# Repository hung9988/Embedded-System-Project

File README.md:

# HUST Embedded Systems Project
This is a project for the course of Embedded Systems at HUST.

## Project Overview
This project focus on the design of a analog macro pad using the Blackpill (STM32F411CEU6) microcontroller. 

## Features
- **Analog Output**: The macro pad can output analog signals.
- **Rapid Trigger**: A feature that allows the macro pad to send a signal immediately when a key is pressed, without waiting for the key to be released.
- **USB HID**: The macro pad will be recognized as a Human Interface Device (HID) by the host computer, allowing it to send key presses and other input events.
- **USB CDC**: The macro pad will support USB Communication Device Class (CDC) for serial communication with the host computer.
- **Macro Support**: The macro pad can be programmed to perform specific actions when certain keys are pressed.
## External Links
- [3D Case Design](https://cad.onshape.com/documents/5e6cfea2e32c850f530cae58/w/579554a927bd0a7730e0b539/e/56addd2516469d5755cfe071?renderMode=0&uiState=685a2b979b232715eddfcd3f)

## Resources

- [How does USB work?](https://www.youtube.com/watch?v=N0O5Uwc3C0o&t=158s)
- [What is Rapid Trigger?](https://www.youtube.com/watch?v=eZENx1T7OLw)

## References

- [Minipad](https://github.com/minipadKB/minipad-firmware)
- [Riskeyboard](https://github.com/riskable/void_switch_65_pct)
- [Macrolev](https://github.com/heiso/macrolev/tree/main)
- [TinyUSB](https://github.com/hathach/tinyusb)
- [USB in a Nutshell](https://www.beyondlogic.org/usbnutshell/usb1.shtml)
- [SSD1306](https://github.com/afiskon/stm32-ssd1306/tree/master)

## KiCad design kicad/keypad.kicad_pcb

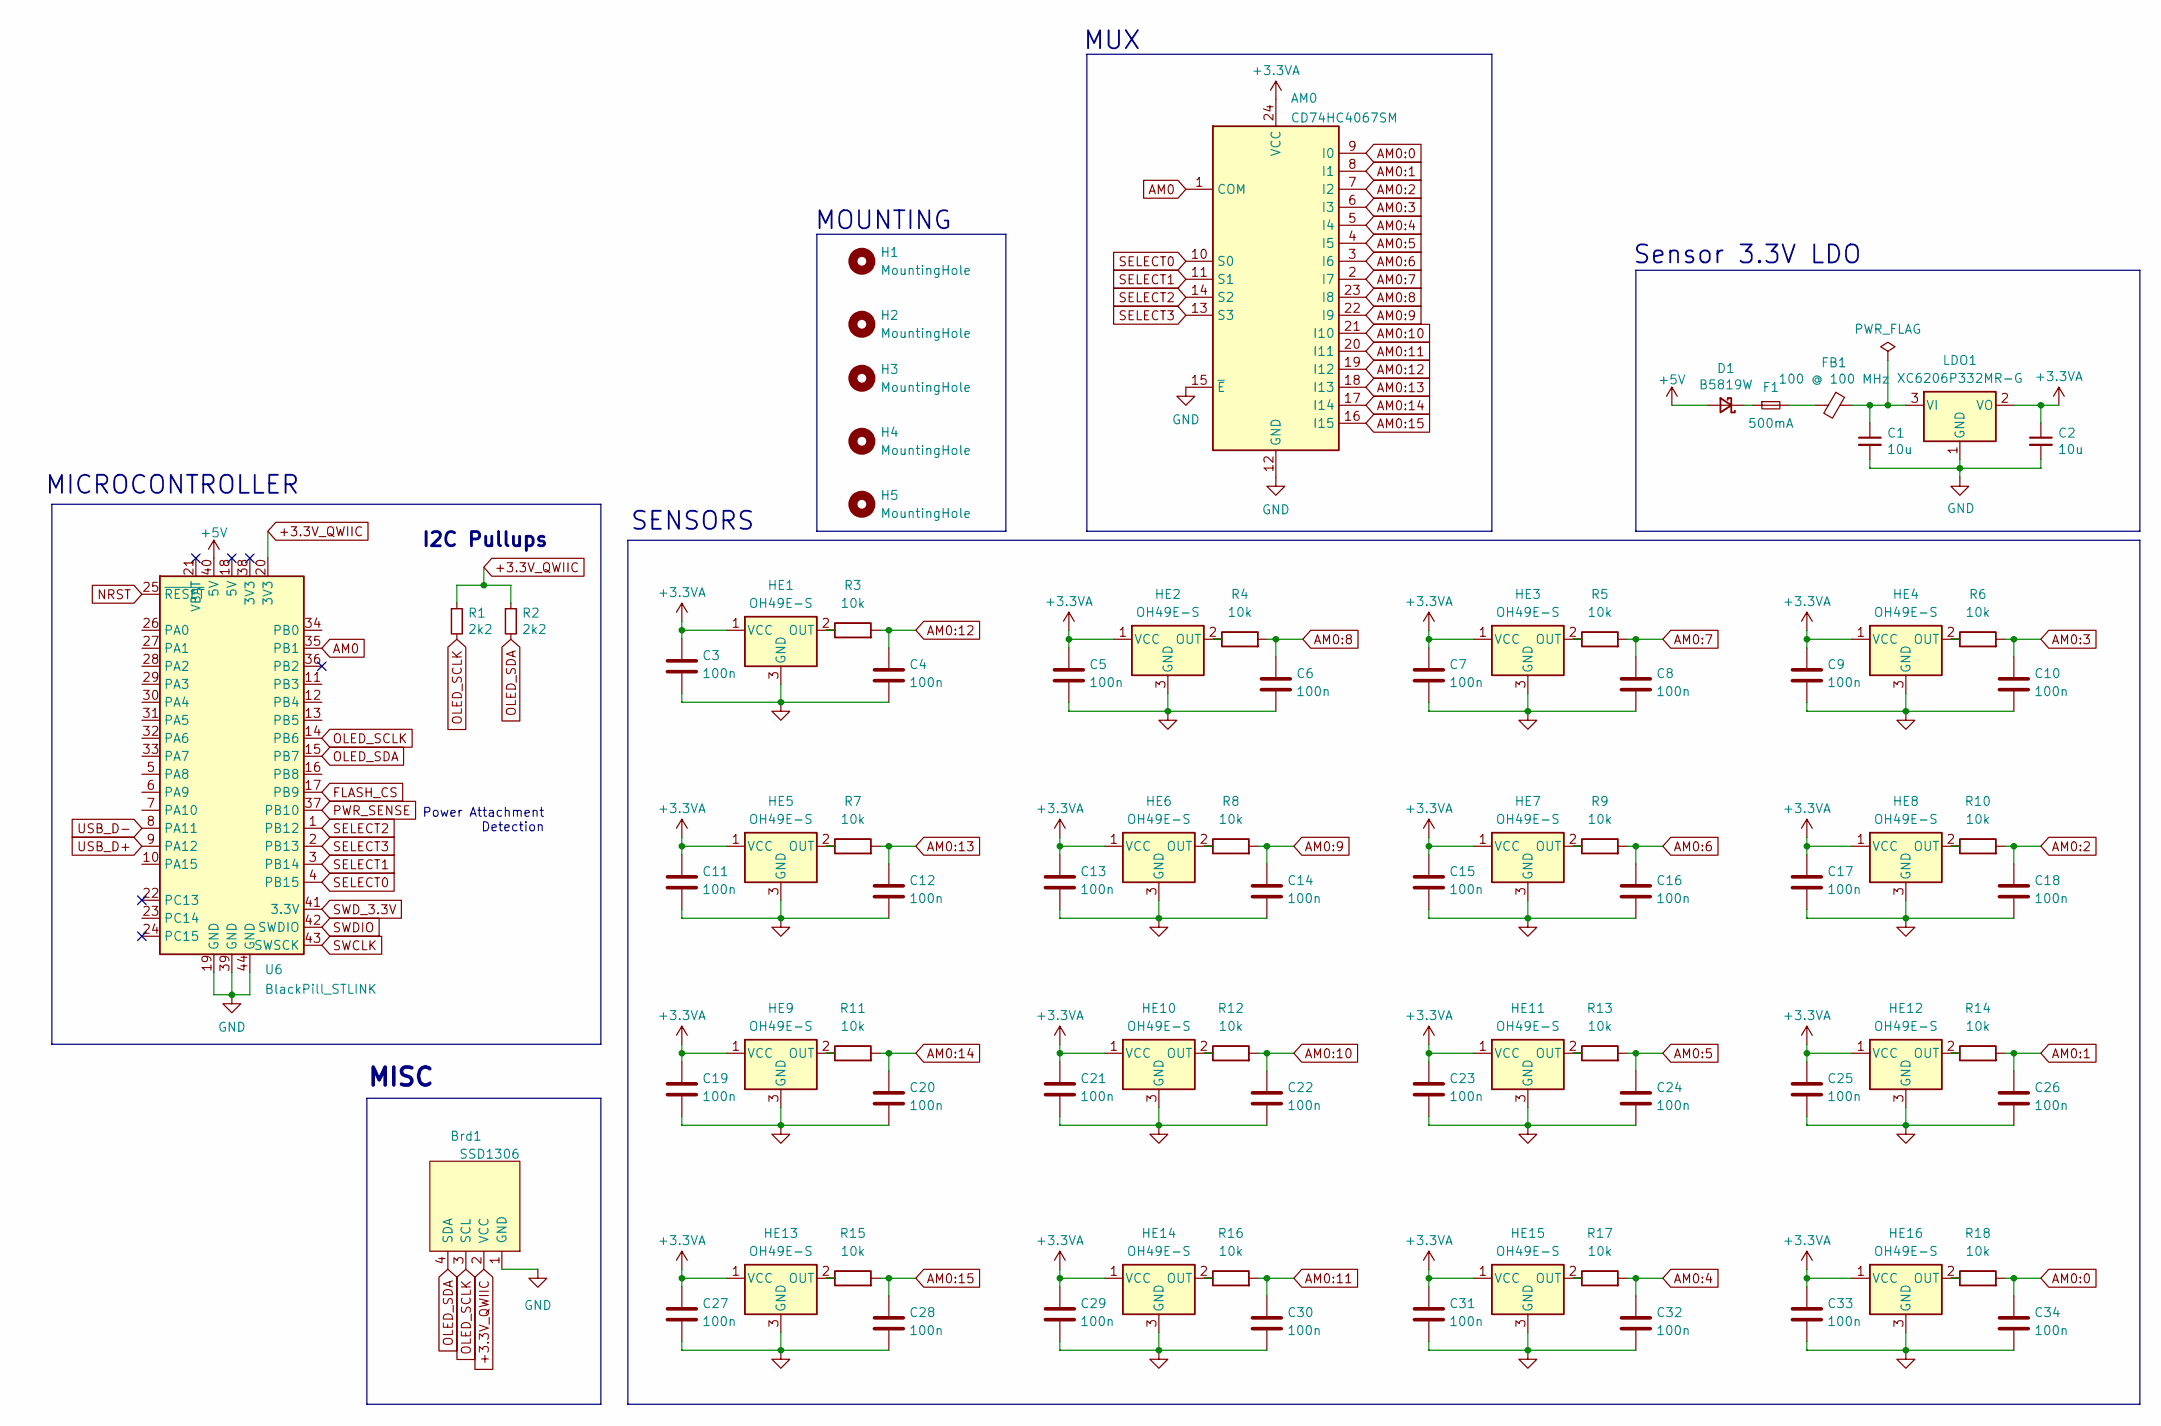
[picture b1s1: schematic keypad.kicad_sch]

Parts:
AM0: CD74HC4067SM; SSOP-24_5.3x8.2mm_P0.65mm
Brd1: SSD1306; 128x64OLED
C1, C2: 10u; C_0402_1005Metric; MPN CL05A106MQ5NUNC; LCSC Part C15525
C3, C4, C5, C6, C7, C8, C9, C10, C11, C12, C13, C14, C15, C16, C17, C18, C19, C20, C21, C22, C23, C24, C25, C26, C27, C28, C29, C30, C31, C32, C33, C34: 100n; C_0402_1005Metric
D1: B5819W; D_SOD-123; MPN B5819W; LCSC Part C8598
F1: 500mA; Fuse_0603_1608Metric; LCSC Part C261937
FB1: 100 @ 100 MHz; L_0805_2012Metric; MPN GZ2012D101TF; LCSC Part C1015
H1, H2, H3, H4, H5: MountingHole; MountingHole_3.2mm_M3_DIN965_Pad
HE1, HE2, HE3, HE4, HE5, HE6, HE7, HE8, HE9, HE10, HE11, HE12, HE13, HE14, HE15, HE16: OH49E-S; SW_MX_HE_0deg_1u
LDO1: XC6206P332MR-G; SOT-23-3; LCSC Part XC6206P332MR-G
R1, R2: 2k2; R_0402_1005Metric; MPN 0402WGF2201TCE; LCSC Part C25879
R3, R4, R5, R6, R7, R8, R9, R10, R11, R12, R13, R14, R15, R16, R17, R18: 10k; R_0402_1005Metric
U6: BlackPill_STLINK

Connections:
+3.3VA: AM0.24 (VCC), C2.1, C3.1, C5.1, C7.1, C9.1, C11.1, C13.1, C15.1, C17.1, C19.1, C21.1, C23.1, C25.1, C27.1, C29.1, C31.1, C33.1, HE1.1 (VCC), HE2.1 (VCC), HE3.1 (VCC), HE4.1 (VCC), HE5.1 (VCC), HE6.1 (VCC), HE7.1 (VCC), HE8.1 (VCC), HE9.1 (VCC), HE10.1 (VCC), HE11.1 (VCC), HE12.1 (VCC), HE13.1 (VCC), HE14.1 (VCC), HE15.1 (VCC), HE16.1 (VCC), LDO1.2 (VO)
+3.3V_QWIIC: Brd1.2 (VCC), R1.1, R2.1, U6.20 (3V3)
+5V: D1.2 (A), U6.40 (5V)
AM0: AM0.1 (COM), U6.35 (PB1)
AM0:0: AM0.9 (I0), C34.1, R18.2
AM0:1: AM0.8 (I1), C26.1, R14.2
AM0:2: AM0.7 (I2), C18.1, R10.2
AM0:3: AM0.6 (I3), C10.1, R6.2
AM0:4: AM0.5 (I4), C32.1, R17.2
AM0:5: AM0.4 (I5), C24.1, R13.2
AM0:6: AM0.3 (I6), C16.1, R9.2
AM0:7: AM0.2 (I7), C8.1, R5.2
AM0:8: AM0.23 (I8), C6.1, R4.2
AM0:9: AM0.22 (I9), C14.1, R8.2
AM0:10: AM0.21 (I10), C22.1, R12.2
AM0:11: AM0.20 (I11), C30.1, R16.2
AM0:12: AM0.19 (I12), C4.1, R3.2
AM0:13: AM0.18 (I13), C12.1, R7.2
AM0:14: AM0.17 (I14), C20.1, R11.2
AM0:15: AM0.16 (I15), C28.1, R15.2
FLASH_CS: U6.17 (PB9)
GND: AM0.12 (GND), AM0.15 (~E), Brd1.1 (GND), C1.2, C2.2, C3.2, C4.2, C5.2, C6.2, C7.2, C8.2, C9.2, C10.2, C11.2, C12.2, C13.2, C14.2, C15.2, C16.2, C17.2, C18.2, C19.2, C20.2, C21.2, C22.2, C23.2, C24.2, C25.2, C26.2, C27.2, C28.2, C29.2, C30.2, C31.2, C32.2, C33.2, C34.2, HE1.3 (GND), HE2.3 (GND), HE3.3 (GND), HE4.3 (GND), HE5.3 (GND), HE6.3 (GND), HE7.3 (GND), HE8.3 (GND), HE9.3 (GND), HE10.3 (GND), HE11.3 (GND), HE12.3 (GND), HE13.3 (GND), HE14.3 (GND), HE15.3 (GND), HE16.3 (GND), LDO1.1 (GND), U6.19 (GND), U6.39 (GND), U6.44 (GND)
NRST: U6.25 (~RESET)
unnamed: D1.1 (K), F1.1
unnamed: F1.2, FB1.2
unnamed: HE1.2 (OUT), R3.1
unnamed: HE2.2 (OUT), R4.1
unnamed: HE3.2 (OUT), R5.1
unnamed: HE4.2 (OUT), R6.1
unnamed: HE5.2 (OUT), R7.1
unnamed: HE6.2 (OUT), R8.1
unnamed: HE7.2 (OUT), R9.1
unnamed: HE8.2 (OUT), R10.1
unnamed: HE9.2 (OUT), R11.1
unnamed: HE10.2 (OUT), R12.1
unnamed: HE11.2 (OUT), R13.1
unnamed: HE12.2 (OUT), R14.1
unnamed: HE13.2 (OUT), R15.1
unnamed: HE14.2 (OUT), R16.1
unnamed: HE15.2 (OUT), R17.1
unnamed: HE16.2 (OUT), R18.1
unnamed: C1.1, FB1.1, LDO1.3 (VI)
OLED_SCLK: Brd1.3 (SCL), R1.2, U6.14 (PB6)
OLED_SDA: Brd1.4 (SDA), R2.2, U6.15 (PB7)
PWR_SENSE: U6.37 (PB10)
SELECT0: AM0.10 (S0), U6.4 (PB15)
SELECT1: AM0.11 (S1), U6.3 (PB14)
SELECT2: AM0.14 (S2), U6.1 (PB12)
SELECT3: AM0.13 (S3), U6.2 (PB13)
SWCLK: U6.43 (SWSCK)
SWDIO: U6.42 (SWDIO)
SWD_3.3V: U6.41 (3.3V)
USB_D+: U6.9 (PA12)
USB_D-: U6.8 (PA11)

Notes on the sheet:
Power Attachment Detection
MUX
I2C Pullups
SENSORS
Sensor 3.3V LDO
MOUNTING
MICROCONTROLLER
MISC

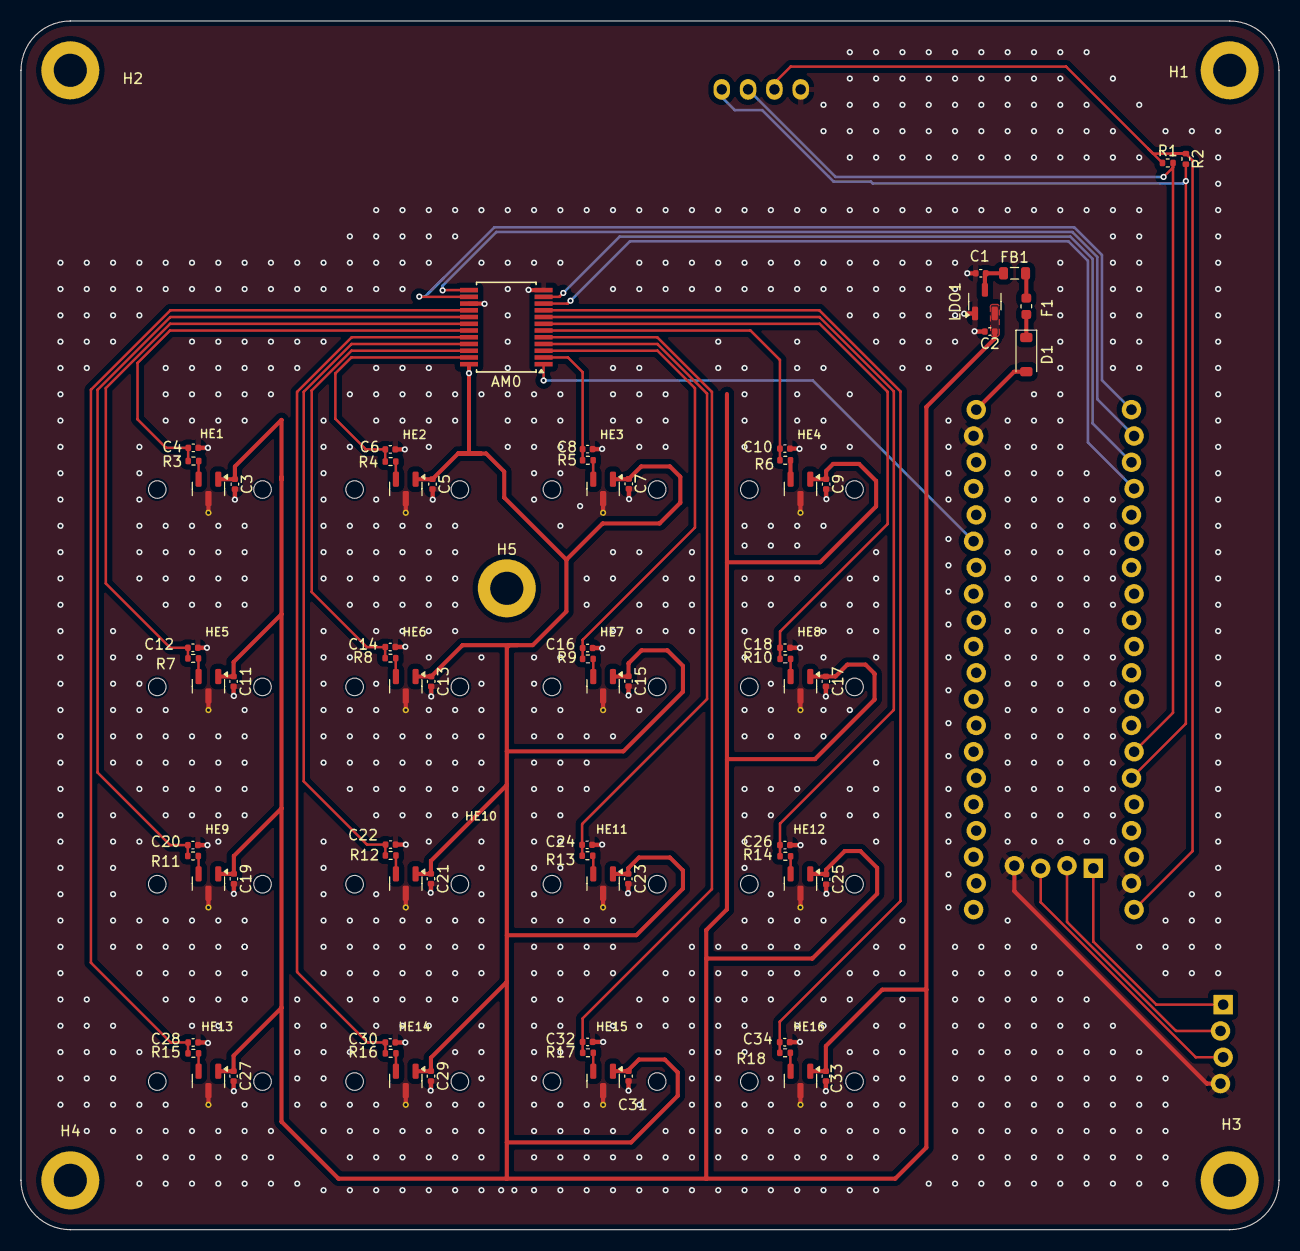
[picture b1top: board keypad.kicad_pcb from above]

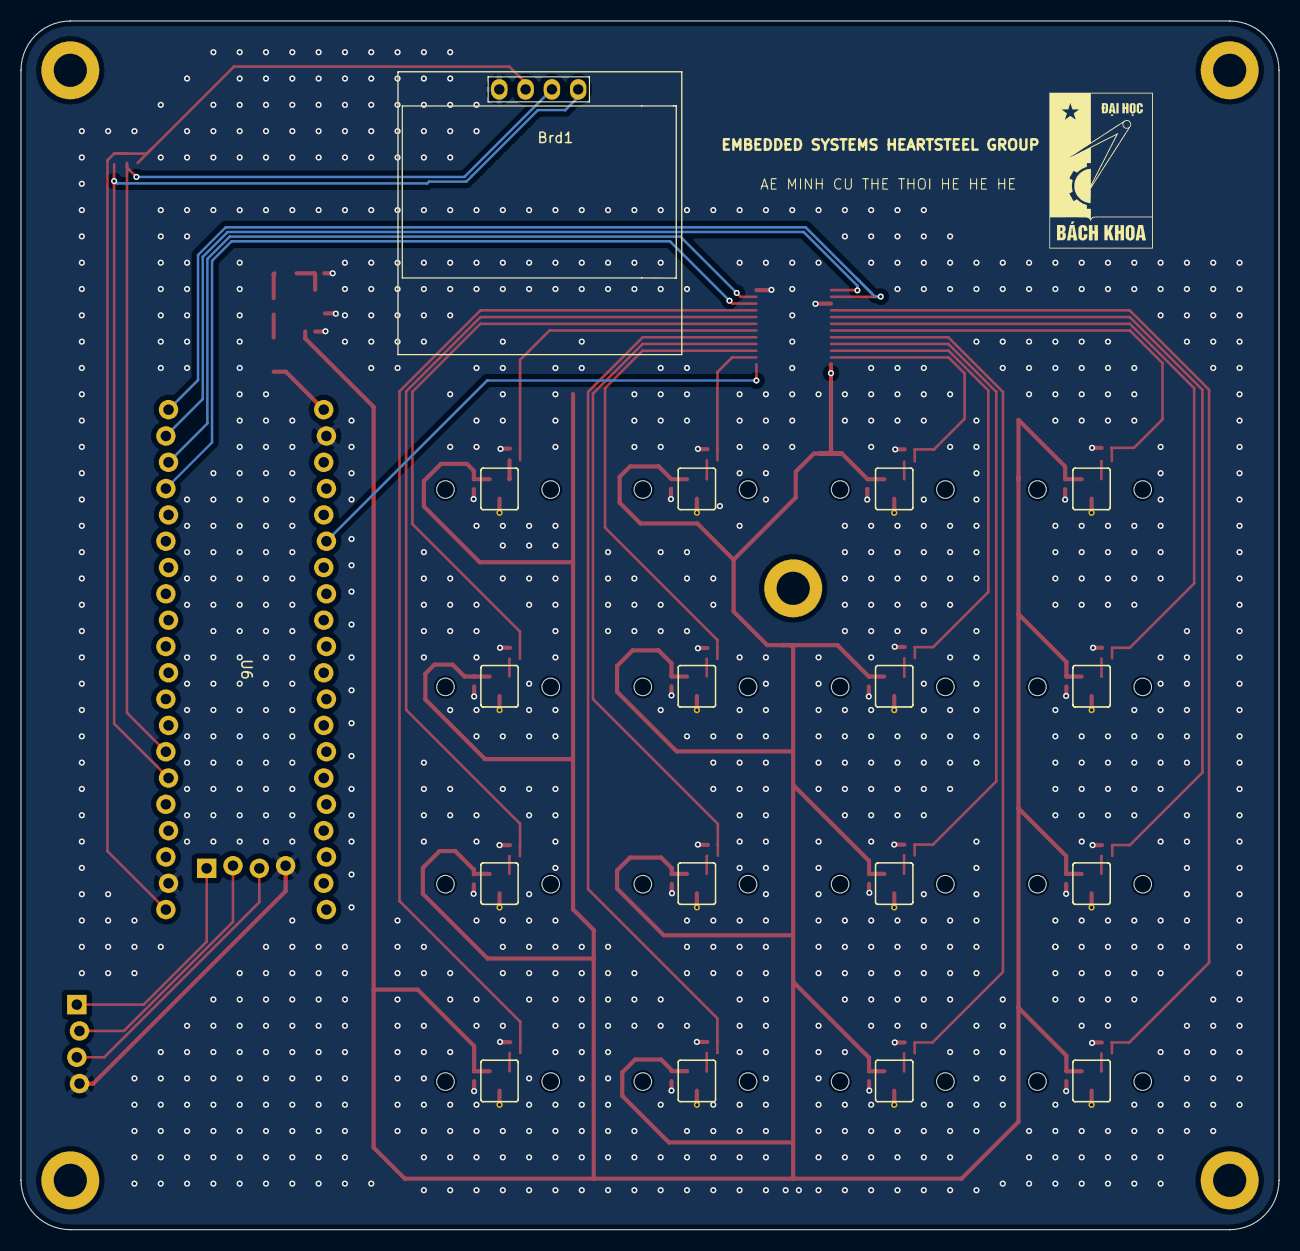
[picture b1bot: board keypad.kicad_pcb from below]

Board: 2 copper layers, 121.4 x 116.7 mm, 80 parts (2 on the bottom side), 46 nets.

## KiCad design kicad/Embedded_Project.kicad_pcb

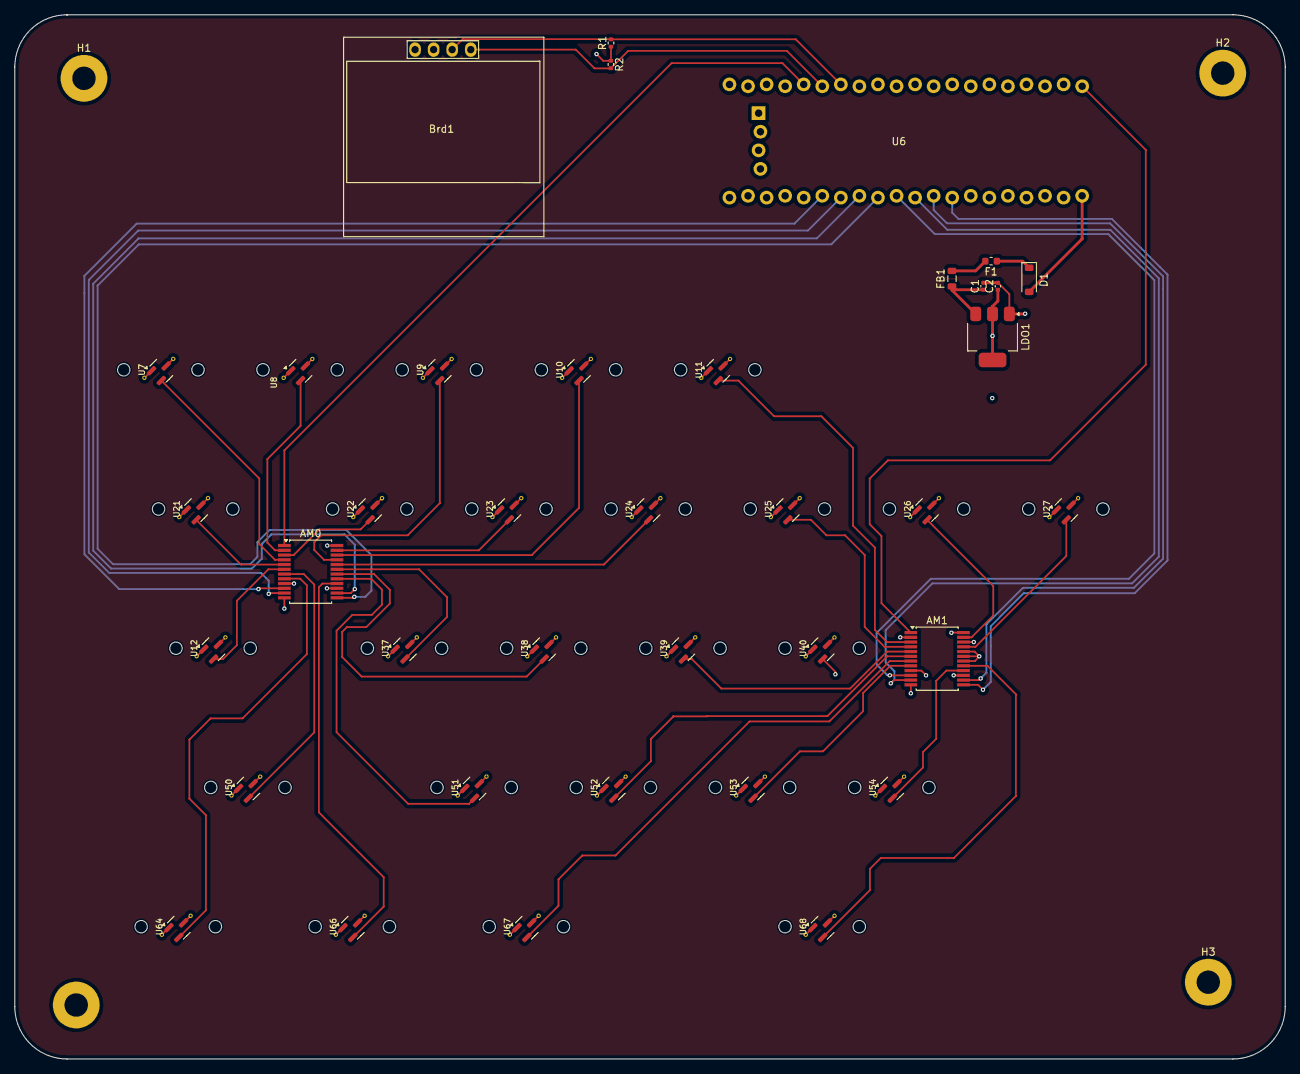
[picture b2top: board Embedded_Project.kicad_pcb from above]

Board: 4 copper layers, 173.8 x 142.9 mm, 42 parts (0 on the bottom side), 45 nets.

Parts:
AM0, AM1: CD74HC4067SM; SSOP-24_5.3x8.2mm_P0.65mm
Brd1: SSD1306; 128x64OLED
C1, C2: 10u; C_0402_1005Metric
D1: B5819W; D_SOD-123
F1: 500mA; Fuse_0603_1608Metric
FB1: 100 @ 100 MHz; L_0805_2012Metric
H1, H2, H3, H4: MountingHole; MountingHole_3.2mm_M3_Pad
LDO1: AMS1117-3.3; SOT-223-3_TabPin2
R1, R2: 2k2; R_0402_1005Metric
U6: BlackPill; BlackPill_STLINK
U7, U8, U9, U10, U11, U22, U23, U24, U25, U26, U27, U37, U38, U39, U40, U51, U52, U53, U54: GH39FKSW; SW_MX_HE_0deg_1u
U12: GH39FKSW; SW_MX_HE_0deg_1.75u
U21: GH39FKSW; SW_MX_HE_0deg_1.5u
U50: GH39FKSW; SW_MX_HE_0deg_2.25
U64, U66, U67: GH39FKSW; SW_MX_HE_0deg_1.25u
U68: GH39FKSW; SW_MX_HE_0deg_3u

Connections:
+3.3V_QWIIC: Brd1.2 (VCC), R1.1, R2.1, U6.20 (3V3)
+3V3: AM0.24 (VCC), AM1.24 (VCC), C2.1, LDO1.2 (VO), U7.1 (VDD), U8.1 (VDD), U9.1 (VDD), U10.1 (VDD), U11.1 (VDD), U12.1 (VDD), U21.1 (VDD), U22.1 (VDD), U23.1 (VDD), U24.1 (VDD), U25.1 (VDD), U26.1 (VDD), U27.1 (VDD), U37.1 (VDD), U38.1 (VDD), U39.1 (VDD), U40.1 (VDD), U50.1 (VDD), U51.1 (VDD), U52.1 (VDD), U53.1 (VDD), U54.1 (VDD), U64.1 (VDD), U66.1 (VDD), U67.1 (VDD), U68.1 (VDD)
+5V: D1.2 (A), U6.40 (5V)
AM0: AM0.1 (COM), U6.16 (PB8)
AM0:1: AM0.8 (I1), U64.2 (OUT)
AM0:2: AM0.7 (I2), U50.2 (OUT)
AM0:3: AM0.6 (I3), U12.2 (OUT)
AM0:4: AM0.5 (I4), U21.2 (OUT)
AM0:5: AM0.4 (I5), U7.2 (OUT)
AM0:6: AM0.3 (I6), U22.2 (OUT)
AM0:7: AM0.2 (I7), U8.2 (OUT)
AM0:8: AM0.23 (I8), U23.2 (OUT)
AM0:9: AM0.22 (I9), U10.2 (OUT)
AM0:10: AM0.21 (I10), U9.2 (OUT)
AM0:11: AM0.20 (I11), U24.2 (OUT)
AM0:12: AM0.19 (I12), U37.2 (OUT)
AM0:13: AM0.18 (I13), U38.2 (OUT)
AM0:14: AM0.17 (I14), U51.2 (OUT)
AM0:15: AM0.16 (I15), U66.2 (OUT)
AM0:SELECT0: AM0.10 (S0), U6.26 (PA0)
AM0:SELECT1: AM0.11 (S1), U6.27 (PA1)
AM0:SELECT2: AM0.14 (S2), U6.28 (PA2)
AM0:SELECT3: AM0.13 (S3), U6.29 (PA3)
AM1: AM1.1 (COM), U6.1 (PB12)
AM1:0: AM1.9 (I0), U40.2 (OUT)
AM1:1: AM1.8 (I1), U53.2 (OUT)
AM1:2: AM1.7 (I2), U67.2 (OUT)
AM1:3: AM1.6 (I3), U52.2 (OUT)
AM1:4: AM1.5 (I4), U39.2 (OUT)
AM1:5: AM1.4 (I5), U25.2 (OUT)
AM1:6: AM1.3 (I6), U11.2 (OUT)
AM1:8: AM1.23 (I8), U26.2 (OUT)
AM1:10: AM1.21 (I10), U27.2 (OUT)
AM1:14: AM1.17 (I14), U68.2 (OUT)
AM1:15: AM1.16 (I15), U54.2 (OUT)
AM1:SELECT0: AM1.10 (S0), U6.30 (PA4)
AM1:SELECT1: AM1.11 (S1), U6.31 (PA5)
AM1:SELECT2: AM1.14 (S2), U6.32 (PA6)
AM1:SELECT3: AM1.13 (S3), U6.33 (PA7)
GND: AM0.9 (I0), AM0.12 (GND), AM0.15 (~E), AM1.2 (I7), AM1.12 (GND), AM1.15 (~E), AM1.18 (I13), AM1.19 (I12), AM1.20 (I11), AM1.22 (I9), Brd1.1 (GND), C1.2, C2.2, LDO1.1 (GND), U6.19 (GND), U6.39 (GND), U6.44 (GND), U7.3 (GND), U8.3 (GND), U9.3 (GND), U10.3 (GND), U11.3 (GND), U12.3 (GND), U21.3 (GND), U22.3 (GND), U23.3 (GND), U24.3 (GND), U25.3 (GND), U26.3 (GND), U27.3 (GND), U37.3 (GND), U38.3 (GND), U39.3 (GND), U40.3 (GND), U50.3 (GND), U51.3 (GND), U52.3 (GND), U53.3 (GND), U54.3 (GND), U64.3 (GND), U66.3 (GND), U67.3 (GND), U68.3 (GND)
unnamed: D1.1 (K), F1.1
unnamed: F1.2, FB1.2
unnamed: C1.1, FB1.1, LDO1.3 (VI)
PB6_SCL1: Brd1.3 (SCL), R1.2, U6.14 (PB6)
PB7_SDA1: Brd1.4 (SDA), R2.2, U6.15 (PB7)

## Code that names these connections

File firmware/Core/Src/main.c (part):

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  /*Configure GPIO pin Output Level */
  HAL_GPIO_WritePin(GPIOB, GPIO_PIN_12 | GPIO_PIN_13 | GPIO_PIN_14 | GPIO_PIN_15, GPIO_PIN_RESET);

  /*Configure GPIO pins : PB12 PB13 PB14 PB15 */
  GPIO_InitStruct.Pin = GPIO_PIN_12 | GPIO_PIN_13 | GPIO_PIN_14 | GPIO_PIN_15;
  GPIO_InitStruct.Mode = GPIO_MODE_OUTPUT_PP;
  GPIO_InitStruct.Pull = GPIO_NOPULL;
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
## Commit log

2025-06-03 Updated references
2025-06-08 upadate kicad pcb
2025-06-11 finished 4x4 pcb design
2025-06-19 get the base code up and running
2025-06-19 fixed keymaps
2025-06-19 Implement SnapTap logic and debug for keyboard
2025-06-19 Added snaptap feature
2025-06-19 Revert "Feat/snaptap"
2025-06-19 Added snaptap mode
2025-06-20 Library added for oled display
2025-06-21 Display functions added for normal keys
2025-06-21 added usb descriptors for cdc + hid composite device and add utils to read COM ports on windows
2025-06-22 fix snaptap
2025-06-22 Display functions added for modifiers
2025-06-22 feat: Add macro support for CTRL+A on key 16
    - Add KEY_TYPE_MACRO enum to support macro keys
    - Implement MACRO_CTRL_A (0xF0) for CTRL+A combination
    - Update init_key() to handle macro keys properly
    - Update hid_press_key() and hid_release_key() to send CTRL+A
    - Fix keymap configuration to use MACRO_CTRL_A for key 16
    - Ensure consistent configuration between keyboard.c and config.c
2025-06-22 Add mode switching snaptap/ combo key mode
2025-06-22 added configuration interface through serial communication with recompiling the firmware
2025-06-22 fixed main import
2025-06-22 added simple cdc performance measure function
2025-06-22 added macro support
2025-06-22 added setmacro commandline in configuration interface
2025-06-23 Optimization
2025-06-23 include mode change and mode notification on hercules
2025-06-23 Redefine keyboard layoutupdate Layer/Mode change key
2025-06-23 Display Optimization
2025-06-23 display optimization v2
2025-06-23 display optimization and fixed modifier display
2025-06-23 grid checking
2025-06-24 updated keyboard config
2025-06-24 updated project configuration
2025-06-24 Updated report and README
2025-06-25 Update report
2025-06-25 Logic final update
2025-06-25 updated minor errors
2025-06-25 Latest Update
2025-07-17 added changes
2025-07-25 refactored project

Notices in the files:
firmware/Core/Src/main.c:
Copyright (c) 2023 STMicroelectronics.
All rights reserved.
This software is licensed under terms that can be found in the LICENSE file
